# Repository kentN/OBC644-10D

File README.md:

# OBC644-10D
ATmega644/1284-based arduino compatible on-board computer Reference Model

----------

## Features ##
- 3.3V system / LVTTL Logic level
- Two user Power Output with ON-OFF Control
- ATmega644P or ATmega1284P, 8MHz
- Size: 45x45mm  pin pitch compatible with UP-204GSR Universal PCB
- microSD hinge socket
- Two SPI ROM Option (FlashROM, FRAM, etc..) support SO8W and SO8N
- MPU-9250 9Dof Sensor
- MS5611  Baromater
- RX8900 RealTime Clock (TCXO) (Backup Battery Option)
- INA226 Current Shunt monitor
- I2C x1, UART x2, SPIx1, UserADCch x8, GPIOx14  

----------

## System Block ##

## PIN Map ##
- VIN has Reverse current protection

----------

## Applications ##

- analog & Motion Datalogger
- Energy Harvest sensor
- DIY Space
- DIY HAB

----------

## Project Environment ##

- KiCad (4.0.x)
- Arduino IDE (1.8.X)
- Sanguino bootloader ( https://github.com/Lauszus/Sanguino )
- SDfatlib 

## Project Status ##

- end of life (EOL)

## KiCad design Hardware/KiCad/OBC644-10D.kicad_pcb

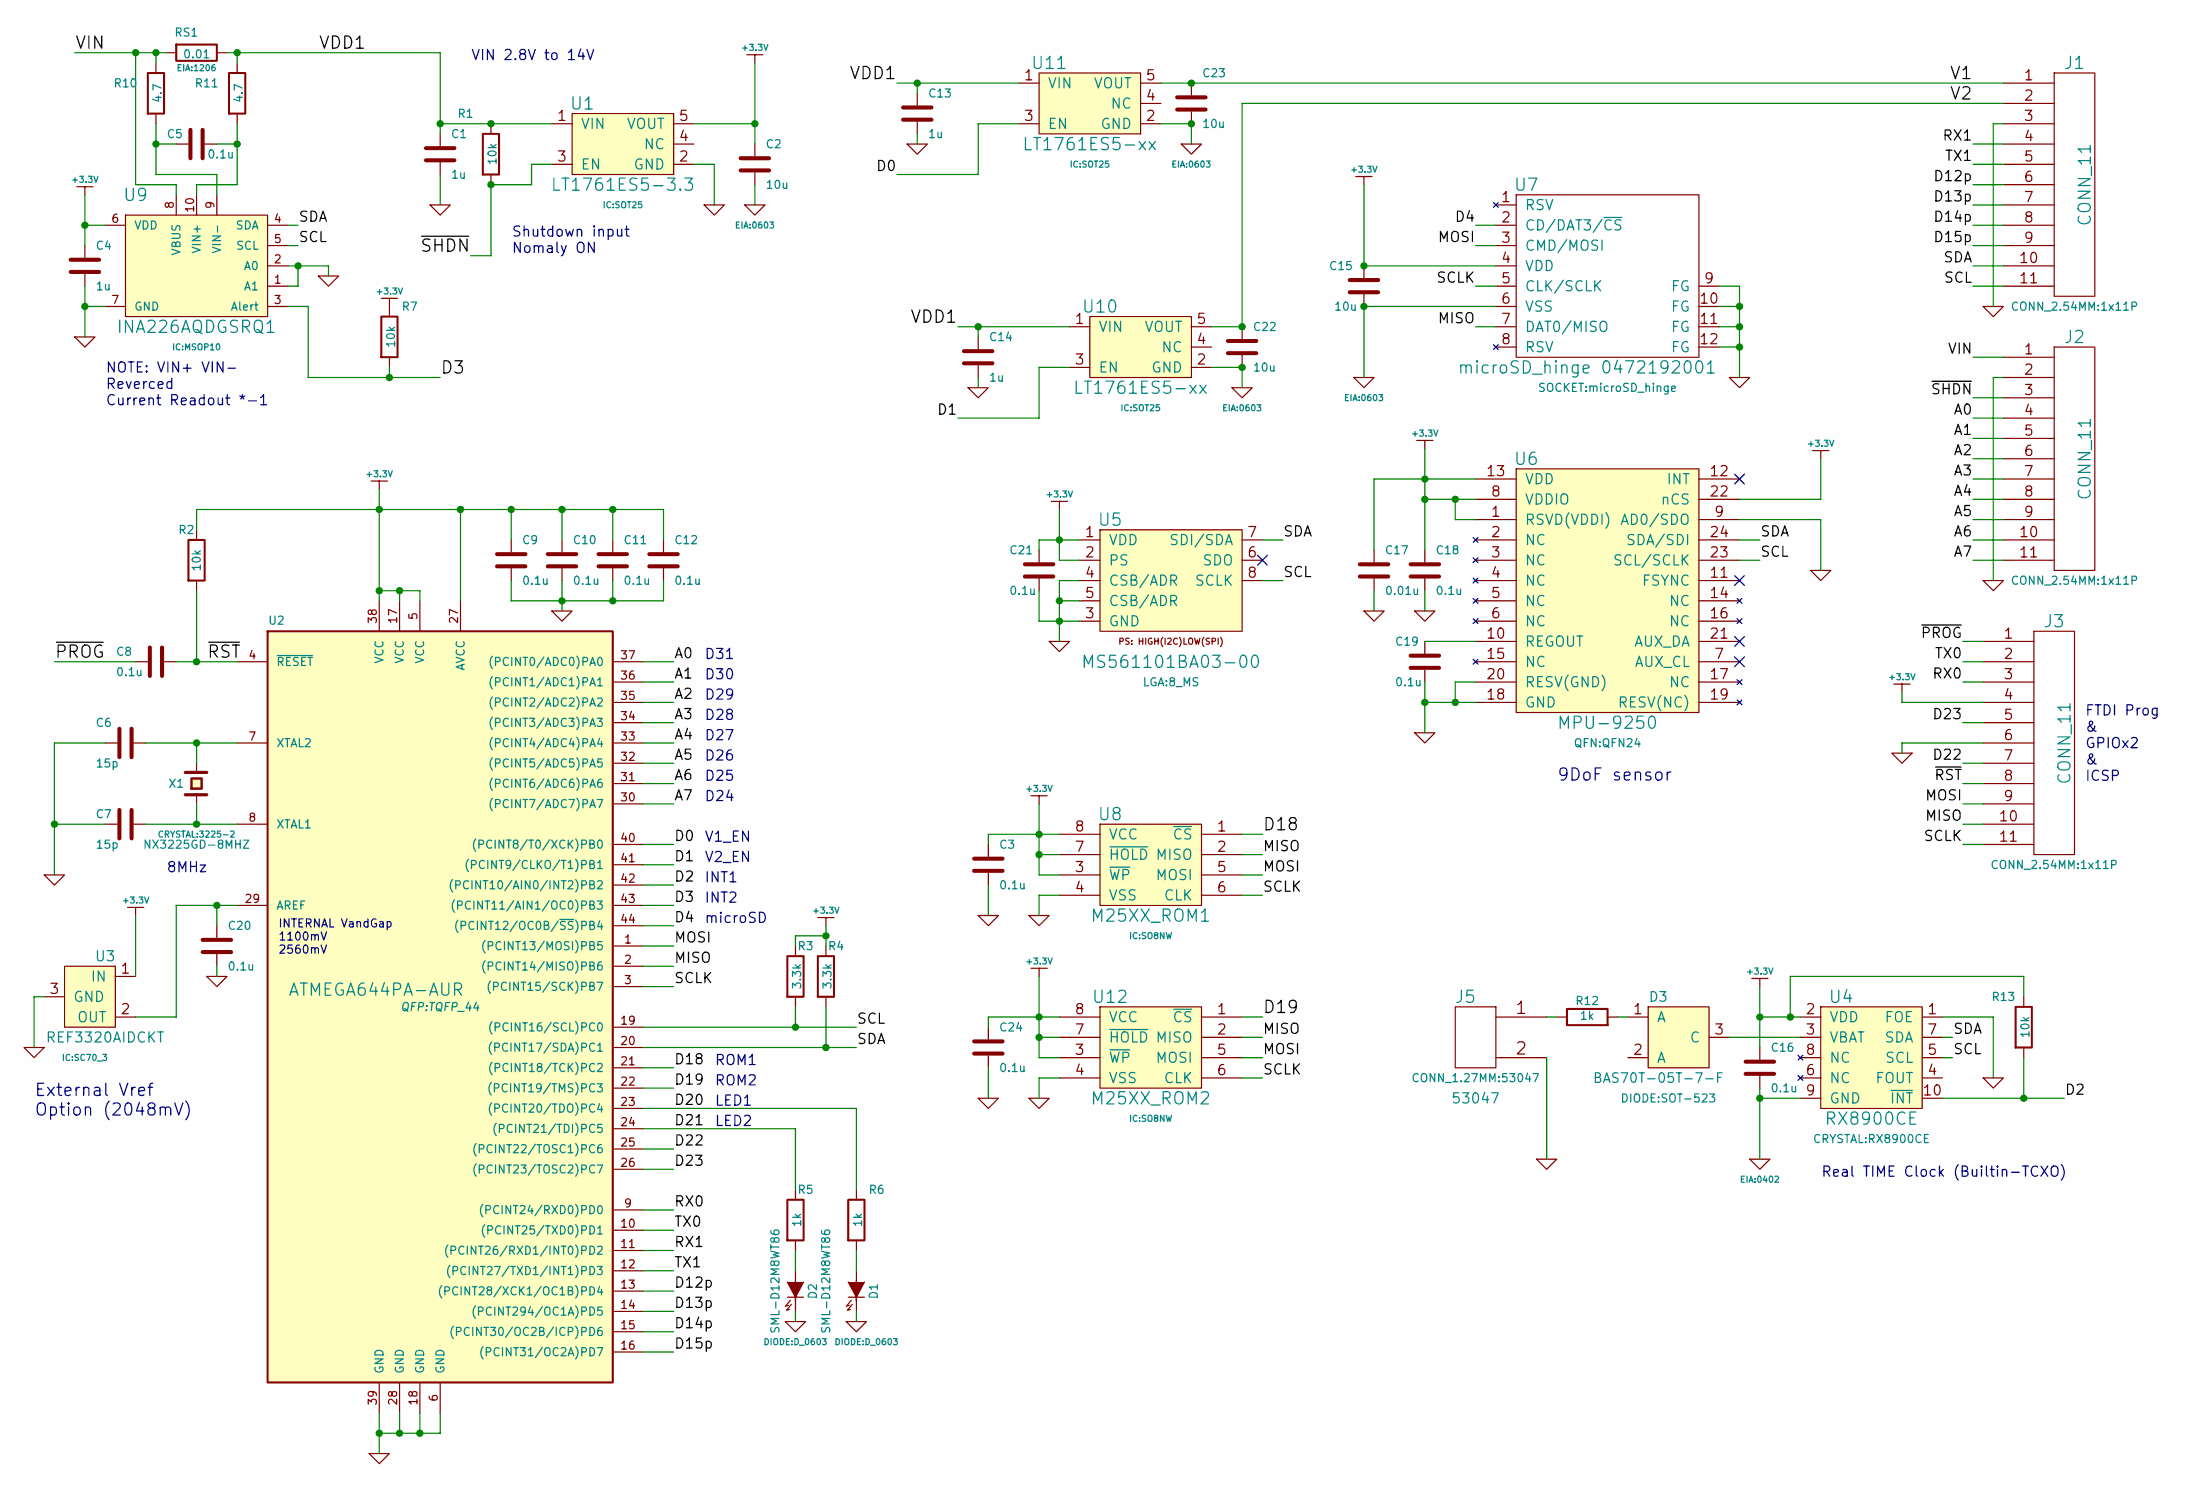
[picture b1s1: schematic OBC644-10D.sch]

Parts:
C1, C4, C13, C14: 1u; 0402
C2, C15, C22, C23: 10u; 0603
C3, C5, C8, C9, C10, C11, C12, C16, C18, C19, C20, C21, C24: 0.1u; 0402
C6, C7: 15p; 0402
C17: 0.01u; 0402
D1, D2: SML-D12M8WT86; D_0603
D3: BAS70T-05T-7-F; SOT-523
J1, J2, J3: CONN_11; 1x11P
J5: 53047
R1, R2, R7, R13: 10k; 0402
R3, R4: 3.3k; 0402
R5, R6, R12: 1k; 0402
R10, R11: 4.7; 0402
RS1: 0.01; 1206
U1: LT1761ES5-3.3; SOT25
U2: ATMEGA644PA-AUR; TQFP_44
U3: REF3320AIDCKT; SC70_3
U4: RX8900CE
U5: MS561101BA03-00; 8_MS
U6: MPU-9250; QFN24
U7: microSD_hinge 0472192001; microSD_hinge
U8: M25XX_ROM1; SO8NW
U9: INA226AQDGSRQ1; MSOP10
U10, U11: LT1761ES5-xx; SOT25
U12: M25XX_ROM2; SO8NW
X1: NX3225GD-8MHZ; 3225-2

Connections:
+3.3V: C2.1, C3.1, C4.1, C9.1, C10.1, C11.1, C12.1, C15.1, C16.1, C17.1, C18.1, C21.1, C24.1, J3.4, R2.1, R3.1, R4.1, R7.1, R13.1, U1.5 (VOUT), U2.5 (VCC), U2.17 (VCC), U2.27 (AVCC), U2.38 (VCC), U3.1 (IN), U4.2 (VDD), U5.1 (VDD), U5.2 (PS), U6.1 (RSVD(VDDI)), U6.8 (VDDIO), U6.13 (VDD), U6.22 (nCS), U7.4 (VDD), U8.3 (~WP~), U8.7 (~HOLD~), U8.8 (VCC), U9.6 (VDD), U12.3 (~WP~), U12.7 (~HOLD~), U12.8 (VCC)
/A0: J2.4, U2.37 ((PCINT0/ADC0)PA0)
/A1: J2.5, U2.36 ((PCINT1/ADC1)PA1)
/A2: J2.6, U2.35 ((PCINT2/ADC2)PA2)
/A3: J2.7, U2.34 ((PCINT3/ADC3)PA3)
/A4: J2.8, U2.33 ((PCINT4/ADC4)PA4)
/A5: J2.9, U2.32 ((PCINT5/ADC5)PA5)
/A6: J2.10, U2.31 ((PCINT6/ADC6)PA6)
/A7: J2.11, U2.30 ((PCINT7/ADC7)PA7)
/D0: U2.40 ((PCINT8/T0/XCK)PB0), U11.3 (EN)
/D1: U2.41 ((PCINT9/CLKO/T1)PB1), U10.3 (EN)
/D2: R13.2, U2.42 ((PCINT10/AIN0/INT2)PB2), U4.10 (~INT)
/D3: R7.2, U2.43 ((PCINT11/AIN1/OC0)PB3), U9.3 (Alert)
/D4: U2.44 ((PCINT12/OC0B/~SS~)PB4), U7.2 (CD/DAT3/~CS~)
/D12p: J1.6, U2.13 ((PCINT28/XCK1/OC1B)PD4)
/D13p: J1.7, U2.14 ((PCINT294/OC1A)PD5)
/D14p: J1.8, U2.15 ((PCINT30/OC2B/ICP)PD6)
/D15p: J1.9, U2.16 ((PCINT31/OC2A)PD7)
/D18: U2.21 ((PCINT18/TCK)PC2), U8.1 (~CS~)
/D19: U2.22 ((PCINT19/TMS)PC3), U12.1 (~CS~)
/D20: R6.1, U2.23 ((PCINT20/TDO)PC4)
/D21: R5.1, U2.24 ((PCINT21/TDI)PC5)
/D22: J3.7, U2.25 ((PCINT22/TOSC1)PC6)
/D23: J3.5, U2.26 ((PCINT23/TOSC2)PC7)
/MISO: J3.10, U2.2 ((PCINT14/MISO)PB6), U7.7 (DAT0/MISO), U8.2 (MISO), U12.2 (MISO)
/MOSI: J3.9, U2.1 ((PCINT13/MOSI)PB5), U7.3 (CMD/MOSI), U8.5 (MOSI), U12.5 (MOSI)
/RX0: J3.3, U2.9 ((PCINT24/RXD0)PD0)
/RX1: J1.4, U2.11 ((PCINT26/RXD1/INT0)PD2)
/SCL: J1.11, R3.2, U2.19 ((PCINT16/SCL)PC0), U4.5 (SCL), U5.8 (SCLK), U6.23 (SCL/SCLK), U9.5 (SCL)
/SCLK: J3.11, U2.3 ((PCINT15/SCK)PB7), U7.5 (CLK/SCLK), U8.6 (CLK), U12.6 (CLK)
/SDA: J1.10, R4.2, U2.20 ((PCINT17/SDA)PC1), U4.7 (SDA), U5.7 (SDI/SDA), U6.24 (SDA/SDI), U9.4 (SDA)
/TX0: J3.2, U2.10 ((PCINT25/TXD0)PD1)
/TX1: J1.5, U2.12 ((PCINT27/TXD1/INT1)PD3)
/V1: C23.1, J1.1, U11.5 (VOUT)
/V2: C22.1, J1.2, U10.5 (VOUT)
/VDD1: C1.1, C13.1, C14.1, R1.1, R11.1, RS1.1, U1.1 (VIN), U10.1 (VIN), U11.1 (VIN)
/VIN: J2.1, R10.1, RS1.2, U9.8 (VBUS)
/~PROG: C8.2, J3.1
/~RST: C8.1, J3.8, R2.2, U2.4 (~RESET)
/~SHDN: J2.3, R1.2, U1.3 (EN)
GND: C1.2, C2.2, C3.2, C4.2, C6.2, C7.2, C9.2, C10.2, C11.2, C12.2, C13.2, C14.2, C15.2, C16.2, C17.2, C18.2, C19.2, C20.2, C21.2, C22.2, C23.2, C24.2, D1.2 (K), D2.2 (K), J1.3, J2.2, J3.6, J5.2 (PM), U1.2 (GND), U2.6 (GND), U2.18 (GND), U2.28 (GND), U2.39 (GND), U3.3 (GND), U4.1 (FOE), U4.9 (GND), U5.3 (GND), U5.4 (CSB/ADR), U5.5 (CSB/ADR), U6.9 (AD0/SDO), U6.18 (GND), U6.20 (RESV(GND)), U7.6 (VSS), U7.9 (FG), U7.10 (FG), U7.11 (FG), U7.12 (FG), U8.4 (VSS), U9.1 (A1), U9.2 (A0), U9.7 (GND), U10.2 (GND), U11.2 (GND), U12.4 (VSS)
unnamed: C5.1, R11.2, U9.10 (VIN+)
unnamed: C5.2, R10.2, U9.9 (VIN-)
unnamed: C6.1, U2.7 (XTAL2), X1.2
unnamed: C7.1, U2.8 (XTAL1), X1.1
unnamed: C19.1, U6.10 (REGOUT)
unnamed: C20.1, U2.29 (AREF), U3.2 (OUT)
unnamed: D1.1 (A), R6.2
unnamed: D2.1 (A), R5.2
unnamed: D3.1 (A), R12.2
unnamed: D3.3 (C), U4.3 (VBAT)
unnamed: J5.1, R12.1

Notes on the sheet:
8MHz
Shutdown input Nomaly ON
VIN 2.8V to 14V
Real TIME Clock (Builtin-TCXO)
9DoF sensor
External Vref Option (2048mV)
INTERNAL VandGap 1100mV 2560mV
ROM1
ROM2
LED2
LED1
INT1
INT2
microSD
V1_EN
V2_EN
D31
D30
D29
D28
D27
D26
D25
D24
NOTE: VIN+ VIN- Reverced Current Readout *-1
FTDI Prog & GPIOx2 & ICSP

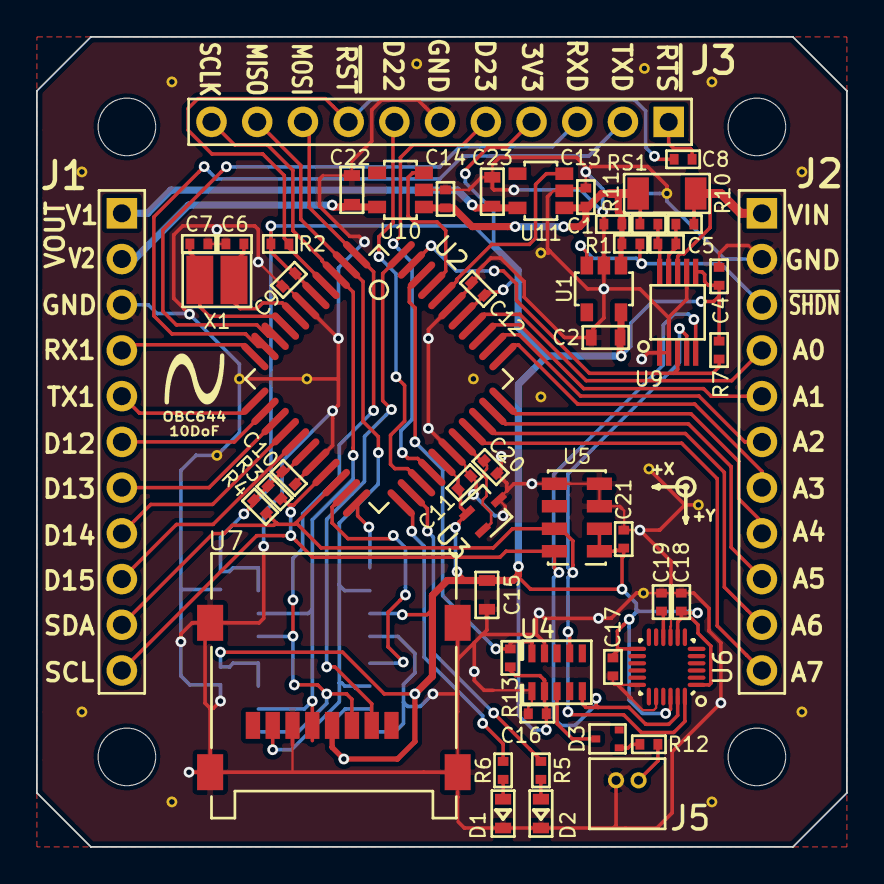
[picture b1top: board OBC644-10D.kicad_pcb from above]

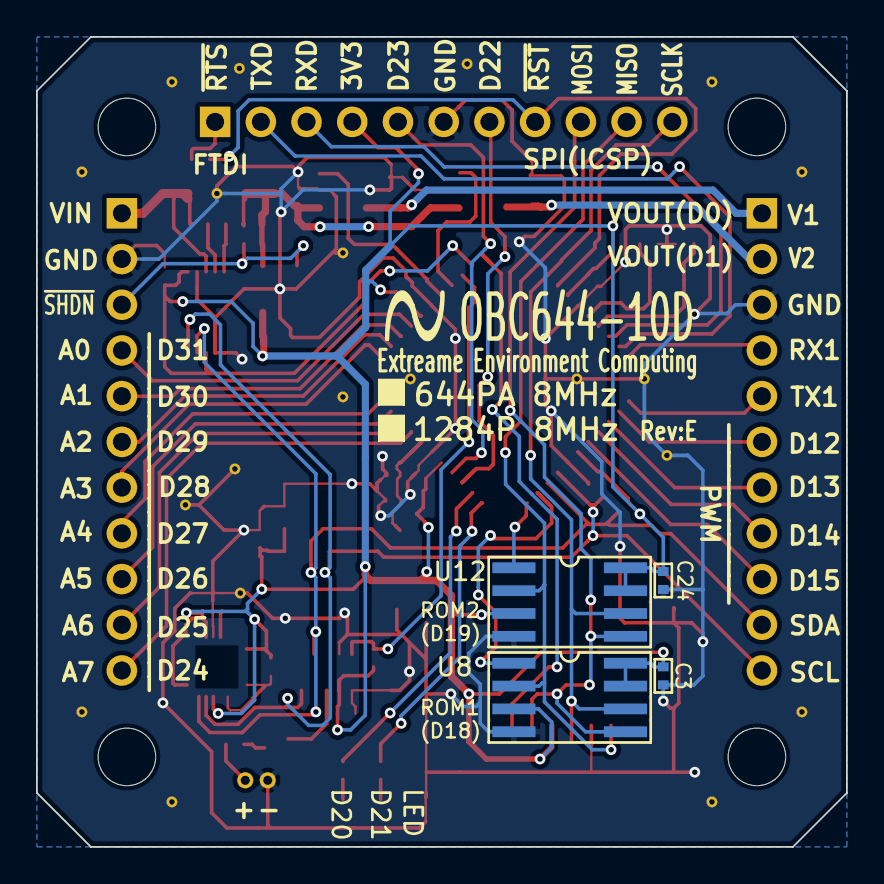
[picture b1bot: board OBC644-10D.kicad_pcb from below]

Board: 2 copper layers, 45.0 x 45.0 mm, 60 parts (4 on the bottom side), 52 nets.

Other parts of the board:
Drill_M3, Drill_M3#2, Drill_M3#3, Drill_M3#4: H**; drill_M3

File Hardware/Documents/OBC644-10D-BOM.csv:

Reference, Value, Footprint, Datasheet
X1,NX3225GD-8MHZ,CRYSTAL:3225-2,
C1,1u,EIA:0402,
C10,0.1u,EIA:0402,
C11,0.1u,EIA:0402,
C12,0.1u,EIA:0402,
C13,1u,EIA:0402,
C14,1u,EIA:0402,
C15,10u,EIA:0603,
C16,0.1u,EIA:0402,
C17,0.01u,EIA:0402,
C18,0.1u,EIA:0402,
C19,0.1u,EIA:0402,
C2,10u,EIA:0603,
C20,0.1u,EIA:0402,
C21,0.1u,EIA:0402,
C22,10u,EIA:0603,
C23,10u,EIA:0603,
C24,0.1u,EIA:0402,
C3,0.1u,EIA:0402,
C4,1u,EIA:0402,
C5,0.1u,EIA:0402,
C6,15p,EIA:0402,
C7,15p,EIA:0402,
C8,0.1u,EIA:0402,
C9,0.1u,EIA:0402,
D1,SML-D12M8WT86,DIODE:0603,
D2,SML-D12M8WT86,DIODE:0603,
D3,BAS70T-05T-7-F,DIODE:SOT523HY,
J1,CONN_11,CONN_2.54MM:1x11P,
J2,CONN_11,CONN_2.54MM:1x11P,
J3,CONN_4,CONN_2.54MM:1x4P,
J4,CONN_6,CONN_2.54MM:1x6DP,
J5,53047,CONN_1.27MM:53047,
R1,10k,EIA:0402,
R10,4.7,EIA:0402,
R11,4.7,EIA:0402,
R12,1k,EIA:0402,
R13,10k,EIA:0402,
R2,10k,EIA:0402,
R3,3.3k,EIA:0402,
R4,3.3k,EIA:0402,
R5,1k,EIA:0402,
R6,1k,EIA:0402,
R7,10k,EIA:0402,
RS1,0.01,EIA:1206,
U1,LT1761ES5-3.3,TI:SOT-25,
U10,LT1761ES5-xx,TI:SOT-25,
U11,LT1761ES5-xx,TI:SOT-25,
U12,M25XX_ROM2,TI:SO8,
U2,ATMEGA644PA-AUR,QFP_QFN:TQFP_44,
U3,REF3320AIDCKT,TI:SC-70,
U4,RX8900CE,CRYSTAL:RX8900CE,
U5,MS561101BA03-00,LGA:8_MS,
U6,MPU-9250,QFP_QFN:QFN24,
U7,microSD_hinge 0472192001,SOCKET:microSD_hinge,
U8,M25XX_ROM1,TI:SO8,
U9,INA226AQDGSRQ1,TI:MSOP10,

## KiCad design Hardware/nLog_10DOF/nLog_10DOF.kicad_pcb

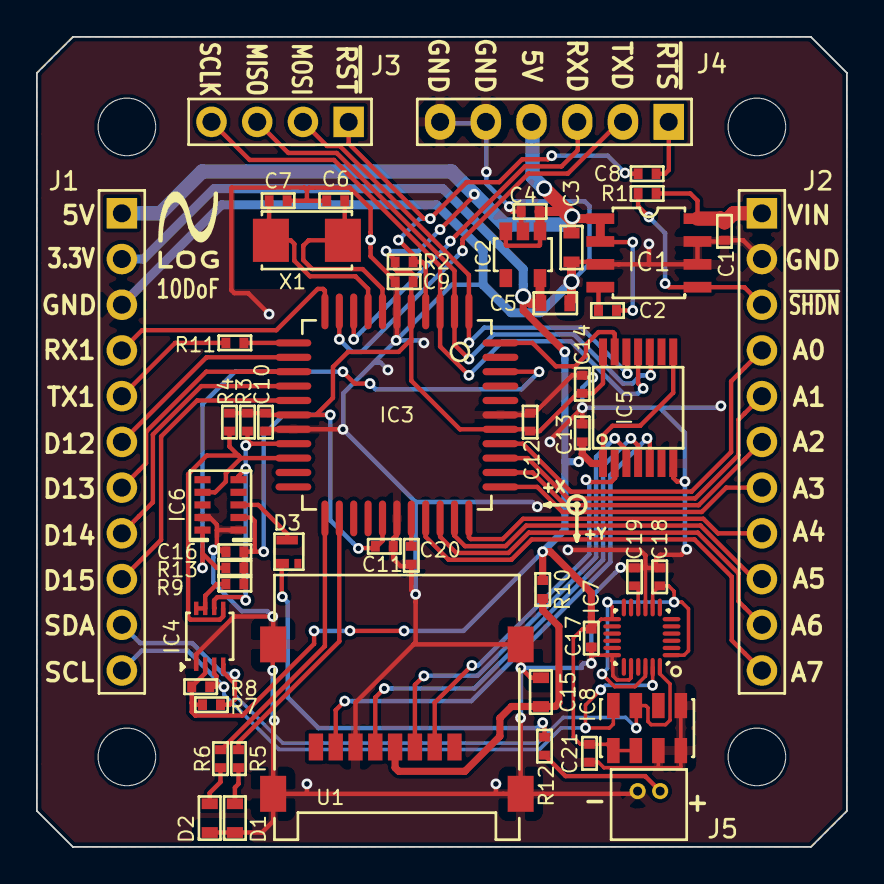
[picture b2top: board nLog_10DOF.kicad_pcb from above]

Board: 2 copper layers, 45.0 x 45.0 mm, 56 parts (0 on the bottom side), 51 nets.

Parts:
C1: 1u; 0402
C2, C17: 0.01u; 0402
C3: 10u; 0603
C4, C8, C9, C10, C11, C12, C13, C14, C16, C18, C19, C20, C21: 0.1u; 0402
C5, C15: 4.7u; 0603
C6, C7: 15p; 0402
D1, D2: LED; 0603
D3: BAS70T-05T-7-F; SOT523HY
Drill_M3, Drill_M3#2, Drill_M3#3, Drill_M3#4: H**; drill_M3
IC1: LT1763-SO8; SO8
IC2: LDO_5; SOT-25
IC3: ATMEGA644PA-A; TQFP_44
IC4: PCA9306; DCU-8
IC5: TXB0104; TSSOP14
IC6: RX8900CE
IC7: MPU-9250; QFN24
IC8: MS5611; 8_MS
J1, J2: CONN_11; 1x11P
J3: CONN_4; 1x4P
J4: CONN_6; 1x6DP
J5: CONN_2; DF13-2P
R1, R2, R13: 10k; 0402
R3, R4, R5, R6, R7, R8: 3.3k; 0402
R9: 200k; 0402
R10: 1; 0402
R11: 100; 0402
R12: 1k; 0402
U1: microSD_hinge
X1: CRYSTAL; 5032

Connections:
+3.3V: C5.1, C13.1, C17.1, C18.1, C21.1, IC2.5, IC4.2, IC5.1, IC5.8, IC7.1, IC7.8, IC7.13, IC7.22, IC8.1, IC8.2, J1.2, R7.1, R8.1, R10.1
+5V: C2.1, C3.1, C4.1, C9.1, C10.1, C11.1, C12.1, C14.1, C16.1, IC1.1, IC1.2, IC2.1, IC2.3, IC3.5, IC3.17, IC3.27, IC3.38, IC5.14, IC6.2, J1.1, J4.4, R2.1, R3.1, R4.1, R9.1, R13.1
/A0: IC3.37, J2.4
/A1: IC3.36, J2.5
/A2: IC3.35, J2.6
/A3: IC3.34, J2.7
/A4: IC3.33, J2.8
/A5: IC3.32, J2.9
/A6: IC3.31, J2.10
/A7: IC3.30, J2.11
/D12p: IC3.13, J1.6
/D13p: IC3.14, J1.7
/D14p: IC3.15, J1.8
/D15p: IC3.16, J1.9
/D20: IC3.23, R6.1
/D21: IC3.24, R5.1
/EN: IC1.5, J2.3, R1.2
/INT: IC3.42, IC6.10, R13.2
/MISO: IC3.2, IC5.10, J3.3
/MISO3V3: IC5.5, U1.7
/MOSI: IC3.1, IC5.12, J3.2
/MOSI3V3: IC5.3, U1.3
/RX0: IC3.9, J4.3
/RX1: IC3.11, J1.4
/SCL: IC3.19, IC4.6, IC6.5, R3.2
/SCL3V3: IC4.3, IC7.23, IC8.8, J1.11, R8.2
/SCLK: IC3.3, IC5.11, J3.4
/SCLK3V3: IC5.4, U1.5
/SDA: IC3.20, IC4.5, IC6.7, R4.2
/SDA3V3: IC4.4, IC7.24, IC8.7, J1.10, R7.2
/TX0: IC3.10, J4.2
/TX1: IC3.12, R11.2
/VIN: C1.1, IC1.8, J2.1, R1.1
/~PROG: C8.2, J4.1
/~RST: C8.1, IC3.4, J3.1, R2.2
/~SS: IC3.44, IC5.13
/~SS3V3: IC5.2, U1.2
GND: C1.2, C3.2, C4.2, C5.2, C6.2, C7.2, C9.2, C10.2, C11.2, C12.2, C13.2, C14.2, C15.2, C16.2, C17.2, C18.2, C19.2, C20.2, C21.2, D1.1, D2.1, IC1.3, IC1.6, IC1.7, IC2.2, IC3.6, IC3.18, IC3.28, IC3.39, IC4.1, IC5.7, IC6.1, IC6.9, IC7.9, IC7.18, IC7.20, IC8.3, IC8.4, IC8.5, J1.3, J2.2, J4.5, J4.6, J5.2, U1.6, U1.9, U1.10, U1.11, U1.12
unnamed: C2.2, IC1.4
unnamed: C6.1, IC3.7, X1.2
unnamed: C7.1, IC3.8, X1.1
unnamed: C15.1, R10.2, U1.4
unnamed: C19.1, IC7.10
unnamed: C20.1, IC3.29
unnamed: D1.2, R5.2
unnamed: D2.2, R6.2
unnamed: D3.1, R12.2
unnamed: D3.3, IC6.3
unnamed: IC4.7, IC4.8, R9.2
unnamed: J1.5, R11.1
unnamed: J5.1, R12.1

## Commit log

2016-09-03 add files
2017-05-18 update HW files
2017-05-18 add image
2017-05-18 add img folder
2017-05-22 fix spacing
2017-06-03 Fix PCB and schematic
    fix ShuntResistor size & routing
    change R5,R6 value
2017-06-04 Add VCPU OUTPUT
    add system voltage output PIN (J6)
2017-06-04 update images
2017-06-04 Add VCPU OUTPUT
2017-06-05 add Photo
2017-06-05 add images
2017-06-05 update image
2017-08-12 Update Rev:E
    Add some Pins (3V3, UART_GPIO)
    Change SO8-ROM Footprints
2017-08-12 update systemblock diagram
2017-08-27 update PCB image(rev:E)
